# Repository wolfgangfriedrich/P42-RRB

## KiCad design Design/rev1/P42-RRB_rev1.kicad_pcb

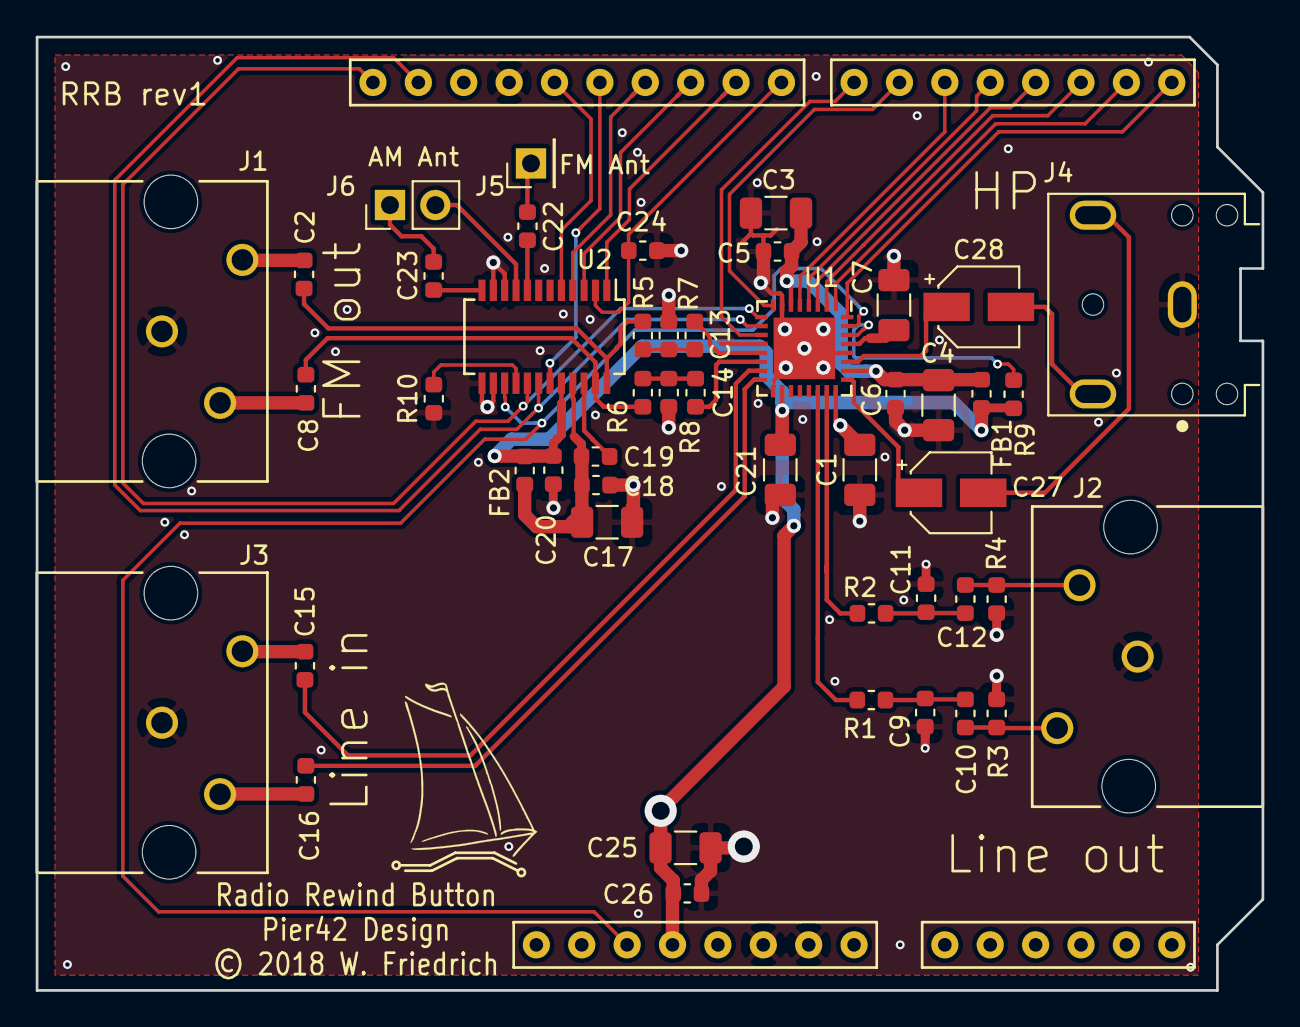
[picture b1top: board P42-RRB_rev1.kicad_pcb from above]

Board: 2 copper layers, 68.6 x 53.3 mm, 49 parts (0 on the bottom side), 53 nets.

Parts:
C1, C3, C4, C7, C17, C25: 10uF; C_1206_3216Metric
C2, C5, C6, C8, C18, C19, C20, C26: 100nF; C_0603_1608Metric
C9, C11: 47nF; C_0603_1608Metric
C10, C12: 1uF; C_0603_1608Metric
C13, C14, C15, C16: 0.47uF; C_0603_1608Metric
C21: 4.7uF; C_1206_3216Metric
C22, C23: 1nF; C_0603_1608Metric
C24: 5pF; C_0603_1608Metric
C27, C28: 47uF; CP_Elec_4x4.5
FB1, FB2: 600R; L_0603_1608Metric
J1: FM out; CUI_RCJ2223
J2: Line out; CUI_RCJ2223
J3: Line in; CUI_RCJ2223
J4: HP; CUI_SJ1-3523N
J5: FM Ant; PinHeader_1x01_P2.54mm_Vertical
J6: AM Ant; PinHeader_1x02_P2.54mm_Vertical
R1, R2: 100R; R_0603_1608Metric
R3, R4: 1K; R_0603_1608Metric
R5, R6: 7K5; R_0603_1608Metric
R7, R8: 2K5; R_0603_1608Metric
R9: 10K; R_0603_1608Metric
R10: 33R; R_0603_1608Metric
SH1: ARDUINO_as_UNO; ARDUINO_as_UNO_R3_CONTOUR
U1: PCM3070; QFN-32-1EP_5x5mm_P0.5mm_EP3.45x3.45mm
U2: Si4731GU; SSOP-24_3.9x8.7mm_P0.635mm

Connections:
+3V3: C20.1, C21.1, C25.1, C26.1, FB1.2, FB2.2, R9.2, SH1.3V3, U1.18, U2.20
/Sheet_Audio_Devices/AM: C23.2, J6.1
/Sheet_Audio_Devices/AMI: C23.1, U2.12
/Sheet_Audio_Devices/AVdd3V3: C1.1, U1.24
/Sheet_Audio_Devices/BCKIN: SH1.2, U1.2
/Sheet_Audio_Devices/DCLK: SH1.10, U2.3
/Sheet_Audio_Devices/DFS: C24.1, SH1.8, U2.2
/Sheet_Audio_Devices/DIN: SH1.4, U1.4
/Sheet_Audio_Devices/DOUT: SH1.5, U1.5
/Sheet_Audio_Devices/DVdd: C7.1, U1.29
/Sheet_Audio_Devices/FM: C22.2, J5.1
/Sheet_Audio_Devices/FMI: C22.1, U2.8
/Sheet_Audio_Devices/FMLO: C2.1, J1.3
/Sheet_Audio_Devices/FMRO: C8.1, J1.2
/Sheet_Audio_Devices/FM_L: C13.2, R5.2, R7.2
/Sheet_Audio_Devices/FM_R: C14.2, R6.2, R8.2
/Sheet_Audio_Devices/GPO1_FM: SH1.13, U2.5
/Sheet_Audio_Devices/HP_L: C27.1, U1.25
/Sheet_Audio_Devices/HP_R: C28.1, U1.27
/Sheet_Audio_Devices/IN1L: C13.1, U1.13
/Sheet_Audio_Devices/IN1R: C14.1, U1.14
/Sheet_Audio_Devices/IN2L: C15.1, U1.15
/Sheet_Audio_Devices/IN2R: C16.1, U1.16
/Sheet_Audio_Devices/LDO_SEL: R9.1, U1.30
/Sheet_Audio_Devices/LDOin-VIO: C3.1, C4.1, C5.1, C6.1, FB1.1, U1.6, U1.26
/Sheet_Audio_Devices/LIL: C15.2, J3.3
/Sheet_Audio_Devices/LINEOUT_L: R1.2, U1.22
/Sheet_Audio_Devices/LINEOUT_R: R2.1, U1.23
/Sheet_Audio_Devices/LIR: C16.2, J3.2
/Sheet_Audio_Devices/LOUT: C2.2, R5.1, U2.24
/Sheet_Audio_Devices/LO_L: C10.1, J2.3, R3.2
/Sheet_Audio_Devices/LO_R: C12.1, J2.2, R4.2
/Sheet_Audio_Devices/LRCIN: SH1.3, U1.3
/Sheet_Audio_Devices/MCLK: SH1.1, U1.1
/Sheet_Audio_Devices/MFP3: SH1.6, U1.8
/Sheet_Audio_Devices/MFP4: SH1.7, U1.11
/Sheet_Audio_Devices/MFP5: SH1.0, U1.32
/Sheet_Audio_Devices/OUT: SH1.9, U2.1
/Sheet_Audio_Devices/RCLK_FM: SH1.12, U2.19
/Sheet_Audio_Devices/RFGND: J6.2, U2.9
/Sheet_Audio_Devices/ROUT: C8.2, R6.1, U2.23
/Sheet_Audio_Devices/SCL: SH1.A5/2, U1.9, U2.17
/Sheet_Audio_Devices/SDA: SH1.A4/2, U1.10, U2.18
/Sheet_Audio_Devices/VA3V3: C17.1, C18.1, C19.1, FB2.1, U2.21
/Sheet_Audio_Devices/nINT_FM: SH1.11, U2.4
/Sheet_Audio_Devices/nRST: SH1.RST, U1.31, U2.15
GND: C1.2, C3.2, C4.2, C5.2, C6.2, C7.2, C9.1, C11.1, C17.2, C18.2, C20.2, C21.2, C24.2, C25.2, C26.2, J1.1, J2.1, J3.1, J4.1, R3.1, R4.1, R7.1, R8.1, R10.1, SH1.GND1, SH1.GND2, SH1.GND3, U1.7, U1.12, U1.17, U1.28, U1.33, U2.10, U2.11, U2.13, U2.14
unnamed: C9.2, C10.2, R1.1
unnamed: C11.2, C12.2, R2.2
unnamed: C19.2, U2.22
unnamed: C27.2, J4.2
unnamed: C28.2, J4.3
unnamed: R10.2, U2.16

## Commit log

2018-08-27 :neckbeard: Added .gitattributes & .gitignore files
2018-08-27 Rev1
    Sch and PCB, Gerber rev1
    Blinky for ARTY-S7 board
2018-09-25 Added files for E14 roadtest
    Added Vivado + design files for RRB FPGA design. (SDRAM not operational
    yet).

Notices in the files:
Design/rev1/P42-RRB_rev1.kicad_pcb:
Creative Commons Attribution - ShareAlike 4.0 International License
This work is licensed under
© 2018 W. Friedrich
